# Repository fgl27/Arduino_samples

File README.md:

Arduino_samples
==============

This is just a random collection of my Arduino scripts/libs, some made by me, some from the web as is, some from the web and modified by me.

If anything here help you enjoy it.

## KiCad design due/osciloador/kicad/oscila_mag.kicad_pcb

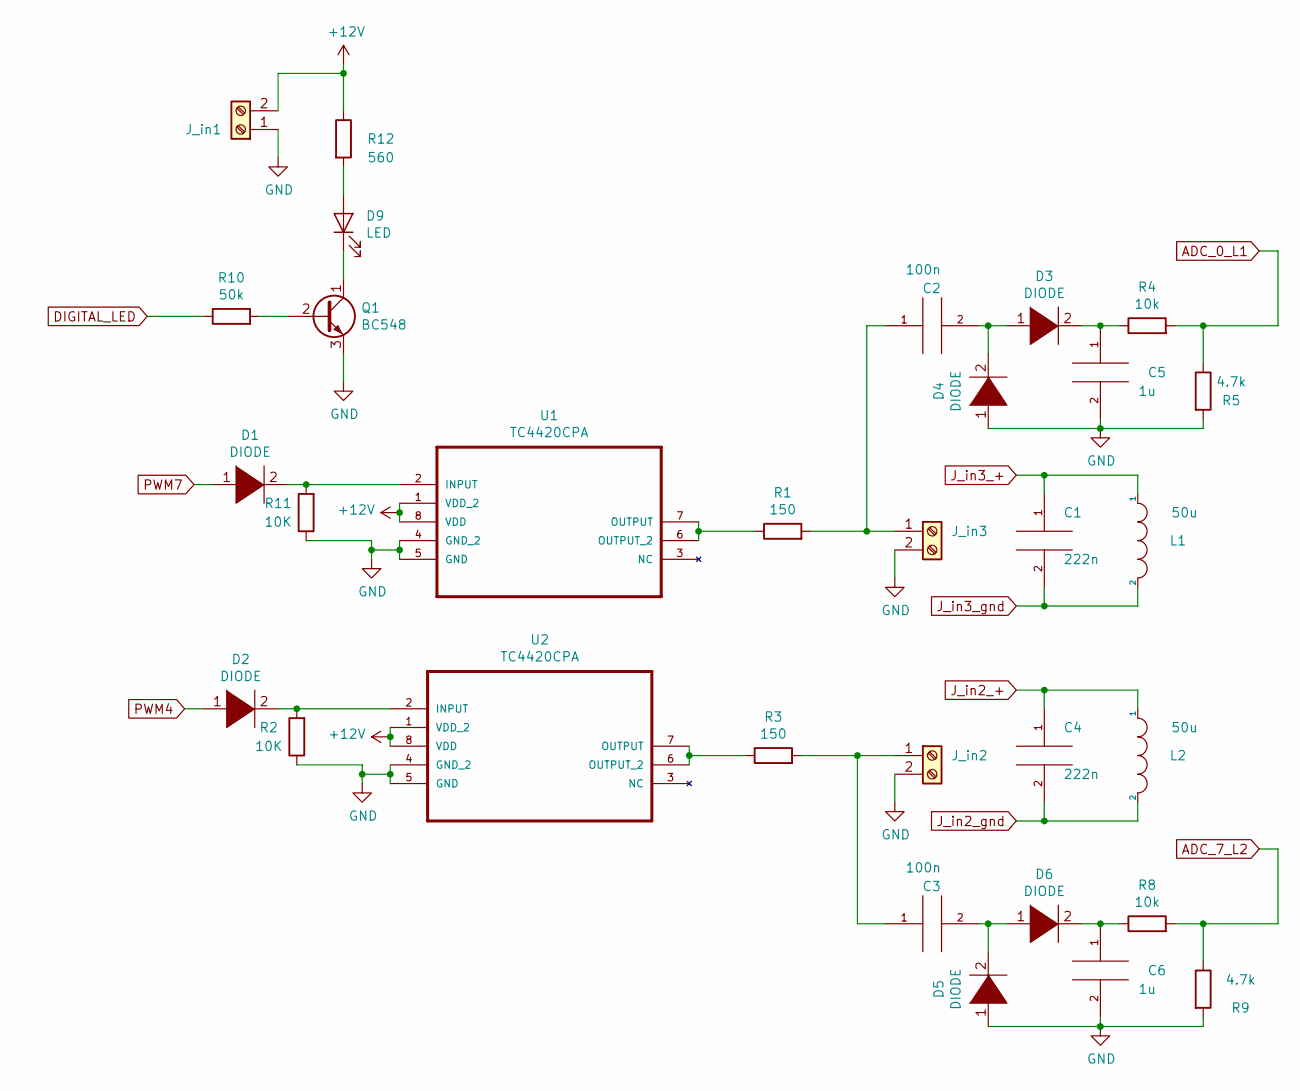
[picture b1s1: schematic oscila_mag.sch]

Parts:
C1, C4: 222n; C_Rect_L7.2mm_W2.5mm_P5.00mm_FKS2_FKP2_MKS2_MKP2
C2, C3: 100n; C_Disc_D8.0mm_W5.0mm_P10.00mm
C5, C6: 1u; C_Disc_D8.0mm_W5.0mm_P10.00mm
D1, D2, D3, D4, D5, D6: DIODE; D_DO-41_SOD81_P12.70mm_Horizontal
D9: LED; LED_D3.0mm_Clear
J_in1, J_in2, J_in3: Screw_Terminal_01x02; TerminalBlock_Altech_AK300-2_P5.00mm
L1, L2: 50u; L_Toroid_Horizontal_D12.7mm_P20.00mm_Diameter14-5mm_Amidon-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
Q1: BC548; TO-92_Inline
R1, R3: 150; R_Axial_DIN0207_L6.3mm_D2.5mm_P10.16mm_Horizontal
R2, R11: 10K; R_Axial_DIN0207_L6.3mm_D2.5mm_P10.16mm_Horizontal
R4, R8: 10k; R_Axial_DIN0207_L6.3mm_D2.5mm_P10.16mm_Horizontal
R5, R9: 4.7k; R_Axial_DIN0207_L6.3mm_D2.5mm_P10.16mm_Horizontal
R10: 50k; R_Axial_DIN0207_L6.3mm_D2.5mm_P10.16mm_Horizontal
R12: 560; R_Axial_DIN0207_L6.3mm_D2.5mm_P10.16mm_Horizontal
U1, U2: TC4420CPA; DIP254P762X533-8

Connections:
+12V: J_in1.2, R12.1, U1.1 (VDD_2), U1.8 (VDD), U2.1 (VDD_2), U2.8 (VDD)
ADC_0_L1: R4.2, R5.1
ADC_7_L2: R8.2, R9.1
DIGITAL_LED: R10.1
GND: C5.2, C6.2, D4.1 (K), D5.1 (K), J_in1.1, J_in2.2, J_in3.2, Q1.3 (E), R2.1, R5.2, R9.2, R11.1, U1.4 (GND_2), U1.5 (GND), U2.4 (GND_2), U2.5 (GND)
J_in2_+: C4.1, L2.1
J_in2_gnd: C4.2, L2.2
J_in3_+: C1.1, L1.1
J_in3_gnd: C1.2, L1.2
unnamed: C2.1, J_in3.1, R1.2
unnamed: C2.2, D3.1 (K), D4.2 (A)
unnamed: C3.1, J_in2.1, R3.2
unnamed: C3.2, D5.2 (A), D6.1 (K)
unnamed: C5.1, D3.2 (A), R4.1
unnamed: C6.1, D6.2 (A), R8.1
unnamed: D1.2 (A), R11.2, U1.2 (INPUT)
unnamed: D2.2 (A), R2.2, U2.2 (INPUT)
unnamed: D9.1 (K), Q1.1 (C)
unnamed: D9.2 (A), R12.2
unnamed: Q1.2 (B), R10.2
unnamed: R1.1, U1.6 (OUTPUT_2), U1.7 (OUTPUT)
unnamed: R3.1, U2.6 (OUTPUT_2), U2.7 (OUTPUT)
PWM4: D2.1 (K)
PWM7: D1.1 (K)

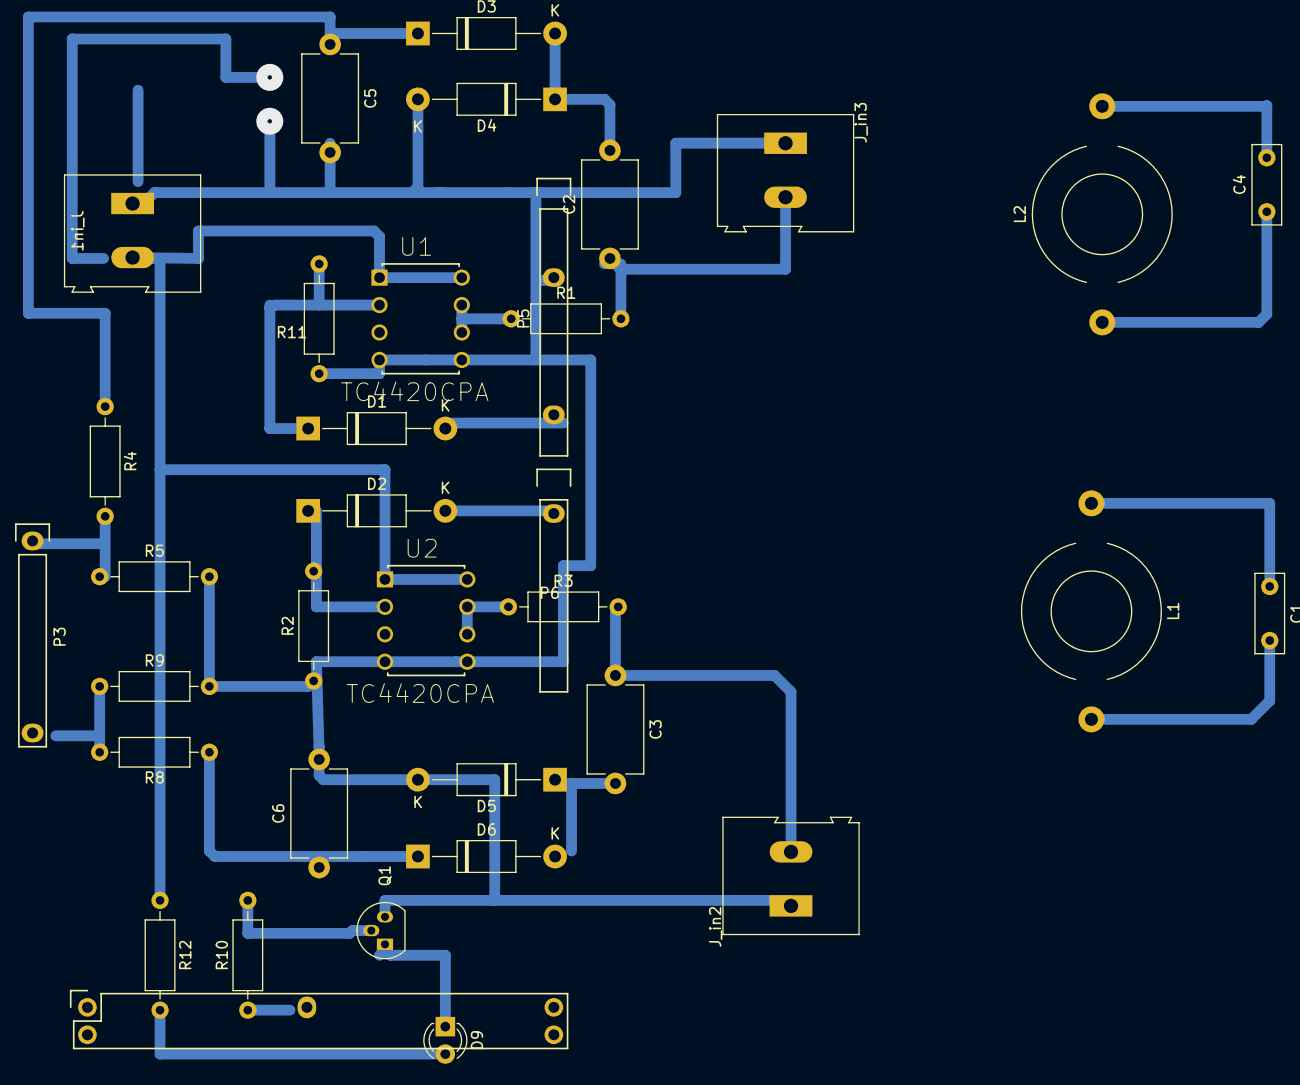
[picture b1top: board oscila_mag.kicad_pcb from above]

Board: 2 copper layers, 35 parts (0 on the bottom side), 21 nets.

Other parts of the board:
ARDUINO DIGITAL I/O: Digital; Socket_Strip_Arduino_2x18
P3: Analog; Socket_Strip_Arduino_1x08
P5: PWM; Socket_Strip_Arduino_1x10
P6: PWM; Socket_Strip_Arduino_1x08

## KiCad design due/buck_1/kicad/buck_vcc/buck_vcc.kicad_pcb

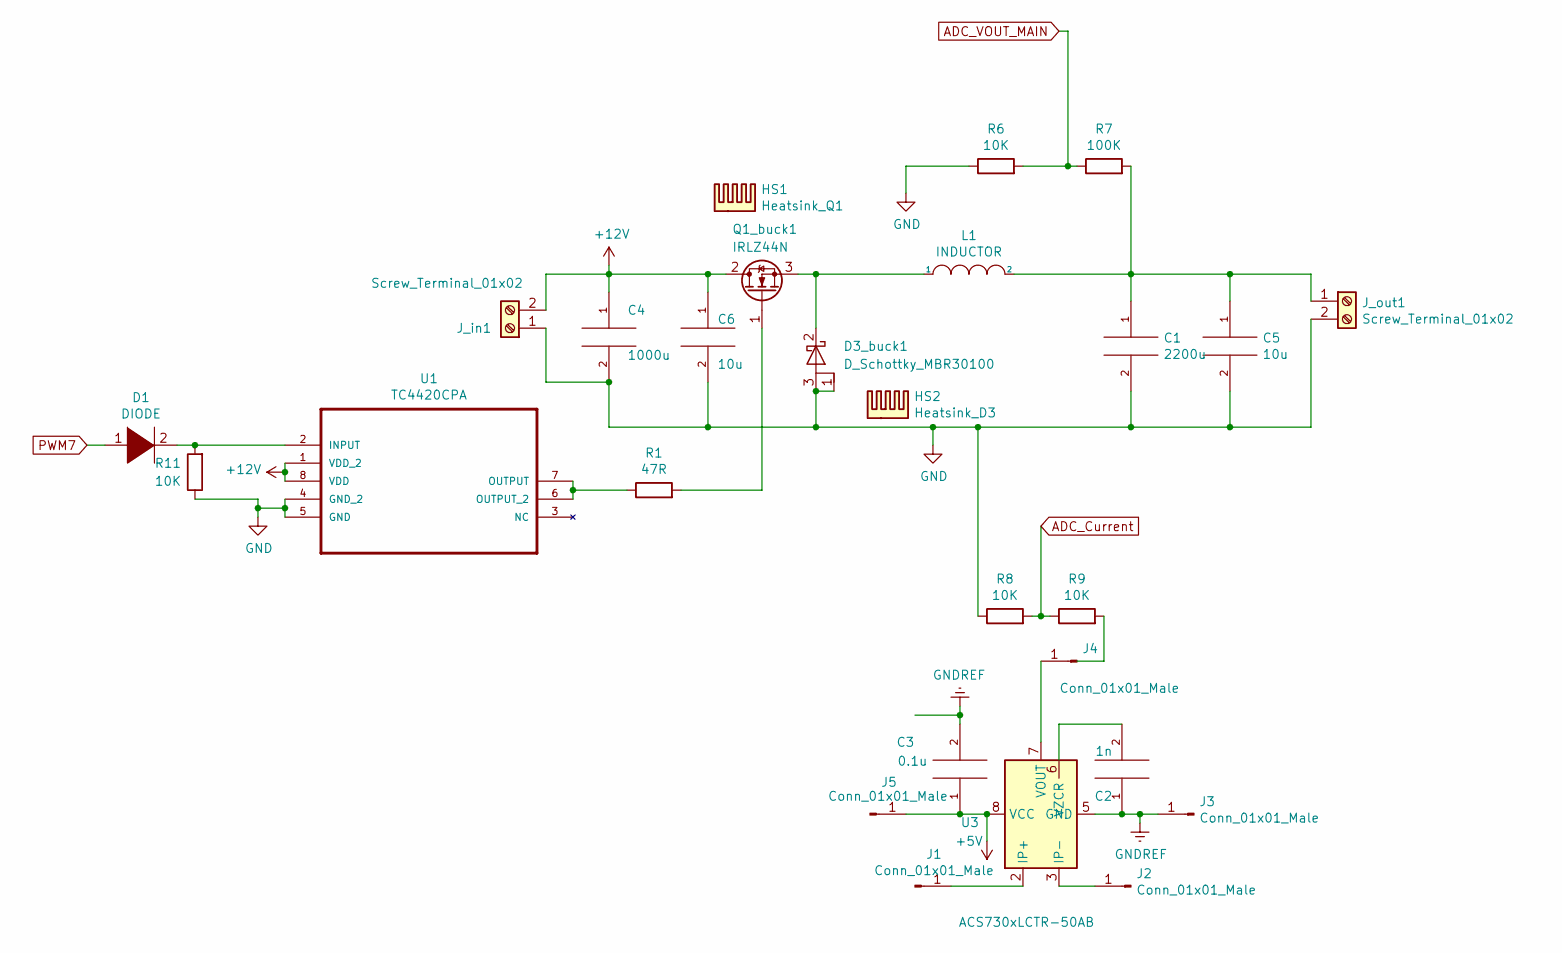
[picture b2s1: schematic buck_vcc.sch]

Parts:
C1: 2200u; C_Radial_D16.0mm_H25.0mm_P7.50mm
C2: 1n; C_Disc_D3.8mm_W2.6mm_P2.50mm
C3: 0.1u; C_Disc_D3.8mm_W2.6mm_P2.50mm
C4: 1000u; C_Radial_D12.5mm_H20.0mm_P5.00mm
C5, C6: 10u; C_Disc_D10.5mm_W5.0mm_P10.00mm
D1: DIODE; D_DO-41_SOD81_P12.70mm_Horizontal
D3_buck1: D_Schottky_MBR30100; TO-220-3_Vertical
HS1: Heatsink_Q1; Heat_Sink_40_40
HS2: Heatsink_D3; Heat_Sink_40_40
J1, J2, J3, J4, J5: Conn_01x01_Male; PinHeader_1x01_P1.00mm_Vertical
J_in1: Screw_Terminal_01x02; TerminalBlock_Altech_AK300-2_P5.00mm
J_out1: Screw_Terminal_01x02; TerminalBlock_Altech_AK300-2_P5.00mm
L1: INDUCTOR; L_Toroid_Vertical_L19.1mm_W8.1mm_P7.10mm_Bourns_5700
Q1_buck1: IRLZ44N; TO-220-3_Vertical
R1: 47R; R_Axial_DIN0207_L6.3mm_D2.5mm_P10.16mm_Horizontal
R6, R8, R9, R11: 10K; R_Axial_DIN0207_L6.3mm_D2.5mm_P10.16mm_Horizontal
R7: 100K; R_Axial_DIN0207_L6.3mm_D2.5mm_P10.16mm_Horizontal
U1: TC4420CPA; DIP254P762X533-8
U3: ACS730xLCTR-50AB; SOIC-8_3.9x4.9mm_P1.27mm

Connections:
+5V: C3.1, J5.1, U3.8 (VCC)
+12V: C4.1, C6.1, J_in1.2, Q1_buck1.2 (D), U1.1 (VDD_2), U1.8 (VDD)
ADC_Current: R8.2, R9.1
ADC_VOUT_MAIN: R6.2, R7.1
GND: C1.2, C4.2, C5.2, C6.2, D3_buck1.1 (A), D3_buck1.3 (A), J_in1.1, J_out1.2, R6.1, R8.1, R11.1, U1.4 (GND_2), U1.5 (GND)
GNDREF: C2.1, C3.2, J3.1, U3.5 (GND)
unnamed: C1.1, C5.1, J_out1.1, L1.2, R7.2
unnamed: C2.2, U3.6 (VZCR)
unnamed: D1.2 (A), R11.2, U1.2 (INPUT)
unnamed: D3_buck1.2 (K), L1.1, Q1_buck1.3 (S)
unnamed: J1.1, U3.1 (IP+), U3.2 (IP+)
unnamed: J2.1, U3.3 (IP-), U3.4 (IP-)
unnamed: J4.1, U3.7 (VOUT)
unnamed: Q1_buck1.1 (G), R1.2
unnamed: R1.1, U1.6 (OUTPUT_2), U1.7 (OUTPUT)
PWM7: D1.1 (K)

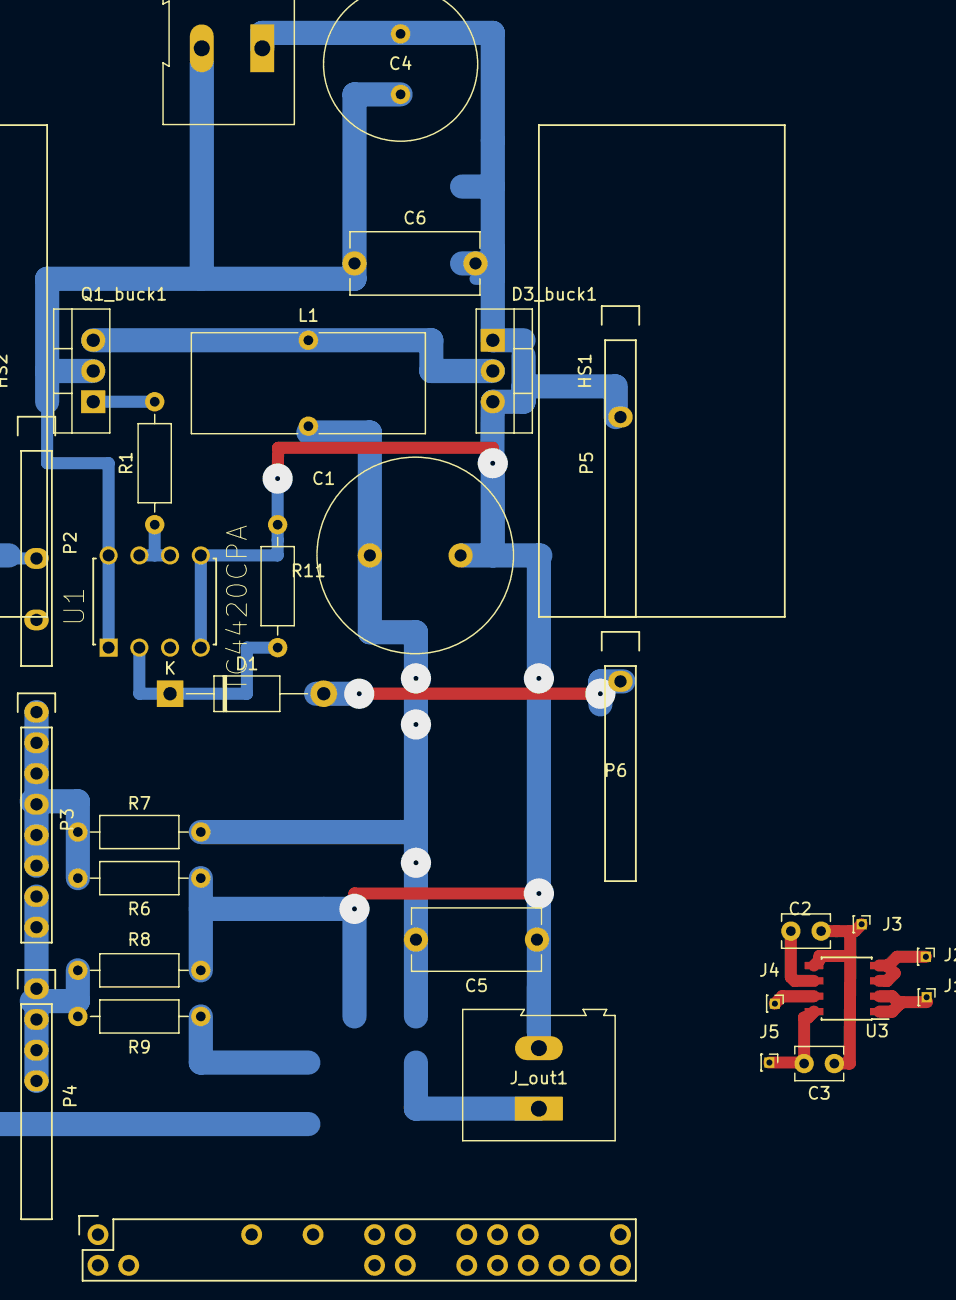
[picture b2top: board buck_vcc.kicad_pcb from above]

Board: 2 copper layers, 33 parts (0 on the bottom side), 15 nets.

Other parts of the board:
ARDUINO DIGITAL I/O: Digital; Socket_Strip_Arduino_2x18
P2: Power; Socket_Strip_Arduino_1x08
P3, P4: Analog; Socket_Strip_Arduino_1x08
P5: PWM; Socket_Strip_Arduino_1x10
P6: PWM; Socket_Strip_Arduino_1x08

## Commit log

2019-04-11 Add README.md
2019-04-11 clean up
2019-04-13 Add .github/auto-comment.yml
2019-04-24 Update due/buck_1 add diagram and kicad file
2019-04-25 due/buck_1/ add matlab files
2019-04-25 Update buck files
2019-06-16 add due/osciloador
2019-06-16 Improve due/osciloador
2019-06-16 Up due/osciloador add kicad files
2019-06-16 Update due/osciloador/kicad/
2019-06-19 Update osciloador and libraries/Adafruit_Circuit_Playground/
2019-06-19 Up due/osciloador
2019-07-21 Up apresentacao
2019-07-21 Add due/update_firm
    to fix reset issue
    reset need to be pressed before use the device when it is powerd by the power port
    this issue is not present when powering from usb
2019-07-21 Up due/update_firm
2021-03-26 Add AM Transmitter Uno sample
2021-05-03 Up samples
2021-05-04 Update AM project
2021-05-04 Up AM image
2021-05-04 Up am/README.md
2021-05-04 Up images AM
2021-05-04 UP am/.gitignore
2021-05-04 add AM due
2021-05-04 UP am uno readme
2021-05-05 Update due am_dac project
2021-05-05 Up due am_dac
2021-05-05 Up due am_dac readme
2021-05-09 Update due am dac
2021-05-09 UP due am dac README.md
2021-05-09 UP due am dac
2021-05-10 Up image due am dac
2021-05-13 Update AM readmes
2021-06-16 Update image am due dac
2021-06-17 Add backup_paginas.txt am due dac
2021-06-17 Up due dac
2021-06-17 Up readme due dac
2021-06-17 Up due dac readme
2021-06-17 Improve comments due dac
2021-06-17 Update image sue dac
2021-06-17 Up am due dac
2021-06-17 Up am due backups
2021-06-17 Update backup am due dac
